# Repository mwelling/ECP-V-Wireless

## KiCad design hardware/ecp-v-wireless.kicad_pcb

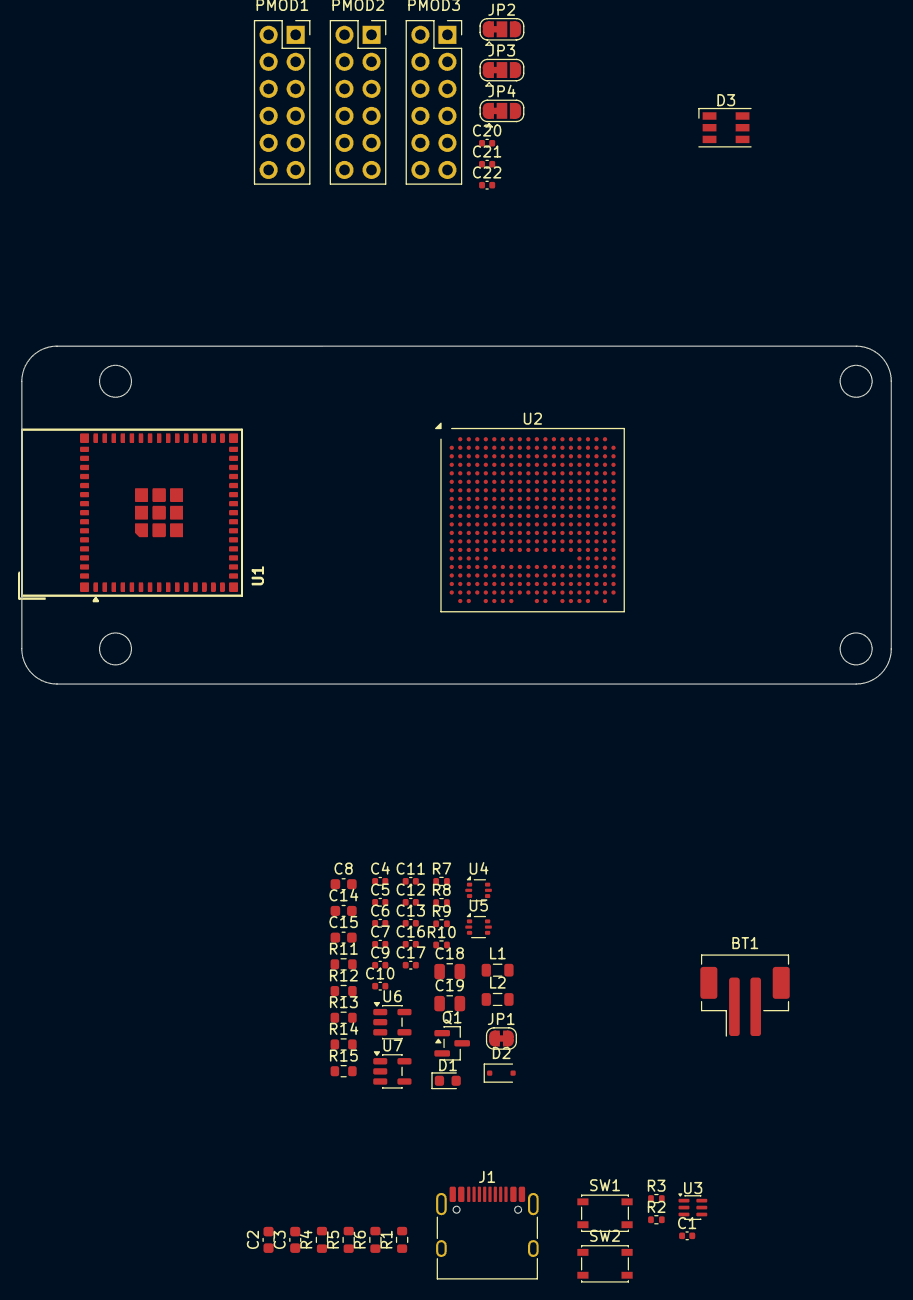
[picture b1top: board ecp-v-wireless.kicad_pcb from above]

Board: 2 copper layers, 81.7 x 31.8 mm, 62 parts (0 on the bottom side), 39 nets, no tracks yet.

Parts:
BT1: Battery Connector; JST_PH_B2B-PH-SM4-TB_1x02-1MP_P2.00mm_Vertical
C1, C20, C21, C22: 0.1uf; C_0402_1005Metric
C2: 1uf; C_0603_1608Metric
C3: 0.01uf; C_0603_1608Metric
C4, C5: 4.7uF; C_0402_1005Metric
C6, C7, C9, C13: 0.1uF; C_0402_1005Metric
C8, C14, C15: 10uF; C_0603_1608Metric
C10, C16, C17: 1uF; C_0402_1005Metric
C11, C12: 6.8pF; C_0402_1005Metric
C18, C19: 10uf; C_0805_2012Metric
D1: LED Yellow; LED_0603_1608Metric
D2: PMEG3020EJ,115; D_SOD-323F
D3: CLX6F-FKC; LED_RGB_PLCC-6
J1: USB_C_Receptacle_USB2.0_16P; USB_C_Receptacle_HRO_TYPE-C-31-M-12
JP1: SolderJumper_2_Bridged; SolderJumper-2_P1.3mm_Bridged_RoundedPad1.0x1.5mm
JP2, JP3, JP4: SolderJumper_3_Bridged12; SolderJumper-3_P1.3mm_Bridged12_RoundedPad1.0x1.5mm
L1, L2: 2.2uH; L_0805_2012Metric
PMOD1, PMOD2, PMOD3: CONN_02X06; PinSocket_2x06_P2.54mm_Vertical
Q1: DMP1045U-7; SOT-23
R1, R11, R12: 10k; R_0603_1608Metric
R2, R3: 27; R_0402_1005Metric
R4, R5: 5.1K; R_0603_1608Metric
R6: 1M; R_0603_1608Metric
R7: 210k; R_0402_1005Metric
R8: 47k; R_0402_1005Metric
R9: 84.5k; R_0402_1005Metric
R10: 100k; R_0402_1005Metric
R13: 1k; R_0603_1608Metric
R14, R15: 100k; R_0603_1608Metric
SW1, SW2: SW_Push; SW_SPST_PTS810
U1, U1#2: ESP32-S3-MINI-1; ESP32-S2-MINI-1
U2: LFE5U-85F-6BG381x; Lattice_caBGA-381_17x17mm_Layout20x20_P0.8mm
U3: DRTR5V0U4S; SOT-363_SC-70-6
U4, U5: TLV62569DRL; SOT-666
U6: TLV713285PDBV; SOT-23-5
U7: MCP73831-2-OT; SOT-23-5

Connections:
+1V1: C6.1, C7.1, C9.1, C12.1, C13.1, C15.1, C17.1, L2.2, R9.2, U2.H8 (VCC), U2.H9 (VCC), U2.H10 (VCC), U2.H11 (VCC), U2.H12 (VCC), U2.H13 (VCC), U2.J8 (VCC), U2.J13 (VCC), U2.K8 (VCC), U2.K13 (VCC), U2.L8 (VCC), U2.L13 (VCC), U2.M8 (VCC), U2.M13 (VCC), U2.N8 (VCC), U2.N9 (VCC), U2.N10 (VCC), U2.N11 (VCC), U2.N12 (VCC), U2.N13 (VCC)
+2V5: C8.1, C10.1, U2.F6 (VCCAUX), U2.F15 (VCCAUX), U2.P6 (VCCAUX), U2.P15 (VCCAUX), U6.5 (OUT)
+3V3: C2.1, C3.1, C11.1, C14.1, C16.1, D3.4 (BA), D3.5 (GA), D3.6 (RA), JP2.1 (A), JP3.1 (A), JP4.1 (A), L1.2, R1.2, R7.2, U1#2.3 (3V3), U6.1 (IN), U6.3 (EN)
+4V: C4.1, C5.1, D2.1 (K), JP2.3 (B), JP3.3 (B), JP4.3 (B), Q1.2 (S), U4.3 (VIN), U4.5 (EN), U5.3 (VIN), U5.5 (EN)
/ESP32-S3/NRST: C1.1, R1.1, SW1.2, U1#2.45 (EN)
/ESP32-S3/RAW_D_N: J1.A7 (D-), J1.B7 (D-), R2.2, U3.6
/ESP32-S3/RAW_D_P: J1.A6 (D+), J1.B6 (D+), R3.2, U3.1
/ESP32-S3/TCK: U1#2.5 (IO1), U2.T5 (TCK)
/ESP32-S3/TDI: U1#2.7 (IO3), U2.R5 (TDI)
/ESP32-S3/TDO: U1#2.8 (IO4), U2.V4 (TDO)
/ESP32-S3/TMS: U1#2.6 (IO2), U2.U5 (TMS)
/ESP32-S3/USB_D_N: R2.1, U1#2.23 (USB_D-)
/ESP32-S3/USB_D_P: R3.1, U1#2.24 (USB_D+)
/MISC-IO/VJ5: C22.1, JP3.2 (C), PMOD3.11, PMOD3.12
/MISC-IO/VJ6: C21.1, JP2.2 (C), PMOD2.11, PMOD2.12
/MISC-IO/VJ7: C20.1, JP4.2 (C), PMOD1.11, PMOD1.12
/POWER/VBAT: BT1.2, C19.1, Q1.3 (D), R14.2, U7.3 (VBAT)
/POWER/VMID: JP1.1 (A), JP1.2 (B), R14.1, R15.2
GND: BT1.1, C1.2, C2.2, C3.2, C4.2, C5.2, C6.2, C7.2, C8.2, C9.2, C10.2, C13.2, C14.2, C15.2, C16.2, C17.2, C18.2, C19.2, C20.2, C21.2, C22.2, J1.A1 (GND), J1.A12 (GND), J1.B1 (GND), J1.B12 (GND), PMOD1.9, PMOD1.10, PMOD2.9, PMOD2.10, PMOD3.9, PMOD3.10, R4.2, R5.2, R6.2, R8.1, R10.1, R11.2, R12.2, R15.1, SW1.1, SW2.1, U1#2.1 (GND), U1#2.2 (GND), U1#2.42 (GND), U1#2.43 (GND), U1#2.46 (GND), U1#2.47 (GND), U1#2.48 (GND), U1#2.49 (GND), U1#2.50 (GND), U1#2.51 (GND), U1#2.52 (GND), U1#2.53 (GND), U1#2.54 (GND), U1#2.55 (GND), U1#2.56 (GND), U1#2.57 (GND), U1#2.58 (GND), U1#2.59 (GND), U1#2.60 (GND), U1#2.61 (GND), U1#2.62 (GND), U1#2.63 (GND), U1#2.64 (GND), U1#2.65 (GND), U2.B7 (GND), U2.B14 (GND), U2.C19 (GND), U2.D4 (GND), U2.F7 (GND), U2.F8 (GND), U2.F13 (GND), U2.F14 (GND), U2.G4 (GND), U2.G6 (GND), U2.G7 (GND), U2.G8 (GND), U2.G9 (GND), U2.G10 (GND), U2.G11 (GND), U2.G12 (GND), U2.G13 (GND), U2.G14 (GND), U2.G15 (GND), U2.G17 (GND), U2.H19 (GND), U2.J2 (GND), U2.J7 (GND), U2.J9 (GND), U2.J10 (GND), U2.J11 (GND), U2.J12 (GND), U2.J14 (GND), U2.K6 (GND), U2.K7 (GND), U2.K9 (GND), U2.K10 (GND), U2.K11 (GND), U2.K12 (GND), U2.K14 (GND), U2.K15 (GND), U2.L9 (GND), U2.L10 (GND), U2.L11 (GND), U2.L12 (GND), U2.M2 (GND), U2.M7 (GND), U2.M9 (GND), U2.M10 (GND), U2.M11 (GND), U2.M12 (GND), U2.M14 (GND), U2.M16 (GND), U2.N6 (GND), U2.N7 (GND), U2.N14 (GND), U2.N15 (GND), U2.P7 (GND), U2.P8 (GND), U2.P11 (GND), U2.P12 (GND), U2.P13 (GND), U2.P14 (GND), U2.R19 (GND), U2.T6 (GND), U2.T7 (GND), U2.T8 (GND), U2.T9 (GND), U2.T10 (GND), U2.T11 (GND), U2.T12 (GND), U2.T13 (GND), U2.T14 (GND), U2.T15 (GND), U2.U6 (GND), U2.U7 (GND), U2.U8 (GND), U2.U9 (GND), U2.U10 (GND), U2.U11 (GND), U2.U12 (GND), U2.U13 (GND), U2.U14 (GND), U2.U15 (GND), U2.V5 (GND), U2.V6 (GND), U2.V7 (GND), U2.V8 (GND), U2.V9 (GND), U2.V10 (GND), U2.V11 (GND), U2.V12 (GND), U2.V13 (GND), U2.V14 (GND), U2.V15 (GND), U2.V16 (GND), U2.V17 (GND), U2.V18 (GND), U2.V19 (GND), U2.V20 (GND), U2.W6 (GND), U2.W7 (GND), U2.W12 (GND), U2.W15 (GND), U2.W16 (GND), U2.W19 (GND), U2.W20 (GND), U2.Y5 (GND), U2.Y6 (GND), U2.Y7 (GND), U2.Y8 (GND), U2.Y11 (GND), U2.Y12 (GND), U2.Y14 (GND), U2.Y15 (GND), U2.Y16 (GND), U2.Y17 (GND), U2.Y19 (GND), U3.2, U4.2 (GND), U5.2 (GND), U6.2 (GND), U7.2 (VSS)
unnamed: D1.1 (K), R13.1
unnamed: J1.A5 (CC1), R4.1
unnamed: J1.B5 (CC2), R5.1
unnamed: J1.SH (SHIELD), R6.1
unnamed: U1.1 (GND), U1.2 (GND), U1.42 (GND), U1.43 (GND), U1.46 (GND), U1.47 (GND), U1.48 (GND), U1.49 (GND), U1.50 (GND), U1.51 (GND), U1.52 (GND), U1.53 (GND), U1.54 (GND), U1.55 (GND), U1.56 (GND), U1.57 (GND), U1.58 (GND), U1.59 (GND), U1.60 (GND), U1.61 (GND), U1.62 (GND), U1.63 (GND), U1.64 (GND), U1.65 (GND)
unnamed: SW2.2, U1#2.4 (IO0)
unnamed: U2.F9 (VCCIO0), U2.F10 (VCCIO0)
unnamed: U2.F11 (VCCIO1), U2.F12 (VCCIO1)
unnamed: U2.H14 (VCCIO2), U2.H15 (VCCIO2), U2.J15 (VCCIO2)
unnamed: U2.L14 (VCCIO3), U2.L15 (VCCIO3), U2.M15 (VCCIO3)
unnamed: U2.L6 (VCCIO6), U2.L7 (VCCIO6), U2.M6 (VCCIO6)
unnamed: U2.H6 (VCCIO7), U2.H7 (VCCIO7), U2.J6 (VCCIO7)
unnamed: U2.P9 (VCCIO8), U2.P10 (VCCIO8)
unnamed: C11.2, R7.1, R8.2, U4.1 (FB)
unnamed: L1.1, U4.4 (SW)
unnamed: C12.2, R9.1, R10.2, U5.1 (FB)
unnamed: L2.1, U5.4 (SW)
unnamed: R12.1, U7.5 (PROG)
unnamed: R13.2, U7.1 (STAT)
VBUS: C18.1, D1.2 (A), D2.2 (A), J1.A4 (VBUS), J1.A9 (VBUS), J1.B4 (VBUS), J1.B9 (VBUS), Q1.1 (G), R11.1, U3.5, U7.4 (VDD)

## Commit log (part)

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2026-06-17 Initial commit ecp-v wireless
2026-06-24 Add schematic sheets and TODOs
2026-06-25 Add block diagram, USB, LiPo MGMT, Regs, etc
